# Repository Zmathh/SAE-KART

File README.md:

# SAE-KART 

Supervision d'un Kart

## Programme ESP32

### Roadmap

- Intégrer les modules testés et validés individuelement dans un même programme principal (main)

- Utilisation d'un module I2C pour la communication UART du module GPS.

- Fix les modules

### Avancée

|    Module     |     Test      |     Notes     |
| ------------- | ------------- |              -|
| MAIN ESP32    | ✅           |Terminé fonctionnel    |
| Dual Core     | ✅           |Terminé fonctionnel (1 loop/coeurs (2) )   |
| GPS           | ✅           |Terminé fonctionnel    |
| Module Lora   | ✅           |Terminé fonctionnel    |
| écran         | ✅           |Terminé fonctionnel    |
| Accel/frein   | ✅           |Terminé fonctionnel    |
| Shift register| ✅           |Terminé fonctionnel    |
| Capteur temperature|🟨       |Manque capteur temp moteur |
| I2C TO UART   | ✅           |Terminé fonctionnel    |
| Capteur fréquence| ✅  |Terminé fonctionnel   |

## SAE-KART LoRa
Simple KiCad design for an Arduino compatible RN2483 (or RN2903) LoRaWA suited for our Project.

Fork of the original [jpmeyers/RN2483shield](https://github.com/jpmeijers/RN2483shield).

***Top board view***

***Bottom board view***

Adjusted to:

 * ignore the 433MHz antenna trace (868MHz only),

### Required Parts for PCB

 * 3× 10k resistors,
 * 1× SMA 868MHz antenna,
 * 1x RN2483 (or RN2903)

### Setting up

WIP
-debug possible

### Schematic

***Schematic***

***PCB***

## Solidworks Case

***Solidworks view***

### RF Impedance Analyser Results

>(R +jX) - Calibrated with 50ohms

> The first version was a bit off, because we didn't follow the [LoRa Module Datasheet](https://ww1.microchip.com/downloads/aemDocuments/documents/OTH/ProductDocuments/DataSheets/RN2483-Low-Power-Long-Range-LoRa-Technology-Transceiver-Module-DS50002346F.pdf), where we have application information for better transmission.
Tiny holes are for [via stitching](https://www.altium.com/documentation/altium-designer/via-stitching-via-shielding-pcb) 

***[Datasheet P.12](https://ww1.microchip.com/downloads/aemDocuments/documents/OTH/ProductDocuments/DataSheets/RN2483-Low-Power-Long-Range-LoRa-Technology-Transceiver-Module-DS50002346F.pdf)***

In the end after testing we are getting better results, better signal strenght and range. So we are certainly closer for a better impedance, but it could be better as the Analyser retrieved us with not perfect transmision Impedence (29.5 +j*92.3) 
## Final result

***Final result***
## Processing 

Despite the use of an LCD arduino screen, we wanted to add a better gauge interface, more customizable so we tried to use processing.
A first sketch code has been written, using an raspberry pi with a raspberry 7" screen.

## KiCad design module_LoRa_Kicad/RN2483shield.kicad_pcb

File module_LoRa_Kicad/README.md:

# SAE-KART LoRa

Simple KiCad design for an Arduino compatible RN2483 (or RN2903) LoRaWA suited for our Project.

Fork of the original [jpmeyers/RN2483shield](https://github.com/jpmeijers/RN2483shield).

***Top board view***

***Bottom board view***

Adjusted to:

 * ignore the 433MHz antenna trace (868MHz only),

## Required Parts for PCB

 * 3× 10k resistors,
 * 1× SMA 868MHz antenna,
 * 1x RN2483 (or RN2903)

## Setting up

WIP
-debug possible

## Schematic

***Schematic***

***PCB***

# Solidworks Case

***Solidworks view***

## RF Impedance Analyser Results

>(R +jX) - Calibrated with 50ohms

> The first version was a bit off, because we didn't follow the [LoRa Module Datasheet](https://ww1.microchip.com/downloads/aemDocuments/documents/OTH/ProductDocuments/DataSheets/RN2483-Low-Power-Long-Range-LoRa-Technology-Transceiver-Module-DS50002346F.pdf), where we have application information for better transmission.
Tiny holes are for [via stitching](https://www.altium.com/documentation/altium-designer/via-stitching-via-shielding-pcb) 

***[Datasheet P.12](https://ww1.microchip.com/downloads/aemDocuments/documents/OTH/ProductDocuments/DataSheets/RN2483-Low-Power-Long-Range-LoRa-Technology-Transceiver-Module-DS50002346F.pdf)***

In the end after testing we are getting better results, better signal strenght and range. So we are certainly closer for a better impedance, but it could be better as the Analyser retrieved us with not perfect transmision Impedence (29.5 +j*92.3) 
## Final result

WIP
***Final result***
# Processing 

Despite the use of an LCD arduino screen, we wanted to add a better gauge interface, more customizable so we tried to use processing.
A first sketch code has been written, using an raspberry pi with a raspberry 7" screen.

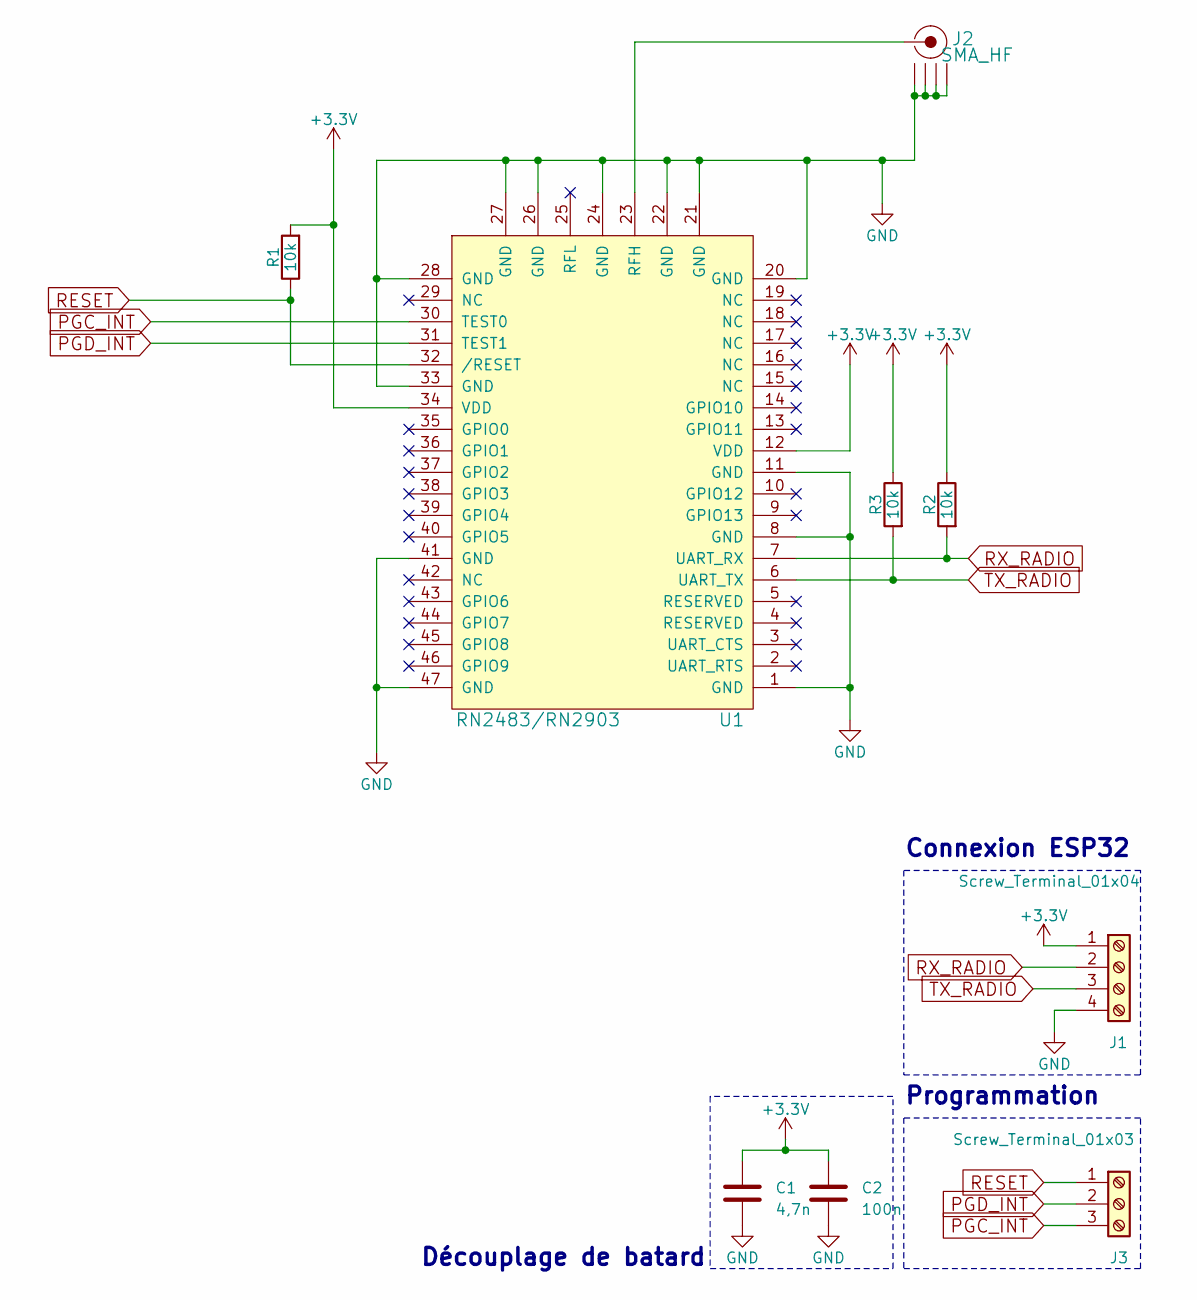
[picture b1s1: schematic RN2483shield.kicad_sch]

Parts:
C1: 4,7n; C_Disc_D3.4mm_W2.1mm_P2.50mm
C2: 100n; C_Disc_D3.4mm_W2.1mm_P2.50mm
J1: Screw_Terminal_01x04; TerminalBlock_TE_282834-4_1x04_P2.54mm_Horizontal
J2: SMA_HF; multi-rf-sma-ufl
J3: Screw_Terminal_01x03; TerminalBlock_TE_282834-3_1x03_P2.54mm_Horizontal
R1, R2, R3: 10k; R_Axial_DIN0207_L6.3mm_D2.5mm_P10.16mm_Horizontal
U1: RN2483/RN2903; RN2483

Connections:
+3V3: C1.1, C2.1, J1.1, R1.2, R2.1, R3.1, U1.12 (VDD), U1.34 (VDD)
GND: C1.2, C2.2, J1.4, J2.2 (GND1), U1.1 (GND), U1.8 (GND), U1.11 (GND), U1.20 (GND), U1.21 (GND), U1.22 (GND), U1.24 (GND), U1.26 (GND), U1.27 (GND), U1.28 (GND), U1.33 (GND), U1.41 (GND), U1.47 (GND)
unnamed: J2.1 (RF), U1.23 (RFH)
PGC_INT: J3.3, U1.30 (TEST0)
PGD_INT: J3.2, U1.31 (TEST1)
RESET: J3.1, R1.1, U1.32 (/RESET)
RX_RADIO: J1.2, R2.2, U1.7 (UART_RX)
TX_RADIO: J1.3, R3.2, U1.6 (UART_TX)

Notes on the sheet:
Connexion ESP32
Programmation
Découplage de batard

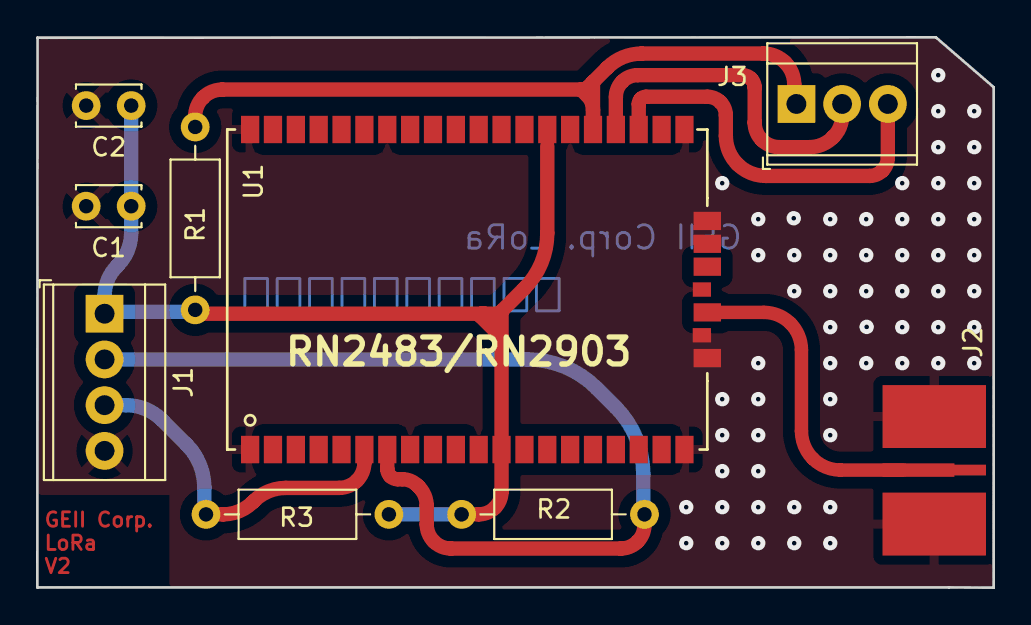
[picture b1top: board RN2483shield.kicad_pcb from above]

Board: 2 copper layers, 53.1 x 30.6 mm, 9 parts (0 on the bottom side), 8 nets.

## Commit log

2023-10-17 kicad
2023-10-17 17/10/2023
2023-10-17 commit 17/10/2023
2023-10-17 cotes
2023-11-27 27/11/2023
2023-11-27 Images updated
2023-11-27 added images
2023-11-27 Added Datasheet image
2023-11-27 Updated images
2023-11-27 Deleted images
2023-11-29 Adding images
2023-11-29 Added processing IHM_Kart
2024-01-30 adding ESP32Code
2024-01-30 ESP32Code
2024-01-30 ReadMe update
2024-01-30 final product images
2024-01-30 coucou
2024-01-30 ivan
2024-01-30 J'ai ajouter bla bla bal
2024-01-30 mathis test
2024-01-30 Ajout des petit code
2024-01-30 Ajout programme principal
2024-01-30 modif
2024-01-30 Template pour les comaintaire
2024-01-30 ajout config_h
2024-01-30 FAUTE
2024-01-30 dedoublage arduino.h
2024-01-30 deplacer
2024-01-30 Estetique
2024-01-30 ajout biblioteque Lecture_Frein_Accel + programme
2024-01-30 VITESSE_SERIAL
2024-01-30 freinaccel
2024-01-30 ajout pins header
2024-01-30 progammer
2024-01-30 sortie Lecture_Frein_Accel
2024-01-30 return
2024-01-30 folder remove
2024-01-30 serial
2024-01-30 vitesse
2024-01-30 Changement biblioteque Lecture_Frein_Accel
2024-01-30 BOOM
2024-01-30 define des varriable
2024-01-30 chinga
2024-01-30 chinfp
2024-01-30 lora
2024-01-30 Degage = et ;
2024-01-30 4 code + main
2024-01-30 samuser
2024-01-30 last 18H
2024-01-30 test
2024-01-30 Ajout des biblioteques en local
2024-01-30 MARCHE
2024-01-30 modif suppr setup/loop dans biblio
2024-01-31 Freq
2024-01-31 GPS NO MORE BROKEN
2024-01-31 Ajout Cpp Mesure_Frequece
2024-01-31 FIcher h de freq
2024-01-31 Reparation librairies LecTemp
2024-01-31 fix lectemp bug
2024-01-31 config tx rx
2024-01-31 main gps
2024-01-31 couco
2024-01-31 sup double gps
2024-01-31 include SoftwareSerial dans main
2024-01-31 SoftwareSerial library for ESP Implemented
2024-01-31 meme chose qu'avant cicular commit pour SofwareSerial
2024-01-31 j'envois
2024-01-31 Fix librairy for project
2024-01-31 BuildPath + 1ere version GPS non valide
2024-01-31 lora modif cpp
2024-01-31 lora test
2024-01-31 ajout librairie lora dans config_h
2024-01-31 Je sais pas
2024-01-31 LORA ok
2024-01-31 moi aussi je fake idle
2024-01-31 dodo
2024-02-03 je degage le temp
2024-02-03 fix build path "build" parent folder
2024-02-03 Ajout librairie écran + Mfréquence (attente librairie LiquidCrystal_I2C et Mfrequence marche pas)
2024-02-03 GPS OK pb buffer réglé
2024-02-03 Serial debug
2024-02-03 shiftReg
2024-02-03 shiftReg Ok a tester lundi
2024-02-03 shift reg main
2024-02-03 shift reg OK
2024-02-03 if endif activate
2024-02-03 config ifdef
2024-02-03 Code écran implémenté fonctionnel
2024-02-03 Ecran fonctionnel
2024-02-03 esthetique config_h
2024-02-03 ajouter entrées écran lcd
2024-02-03 Comments
2024-02-04 Implémentation du Dual Core
2024-02-04 changement delay
2024-02-05 fix Activate_Serial
2024-02-05 fix lecture temps main
2024-02-06 capteur temp test + update Readme
2024-02-06 fix ReadMe
2024-02-06 committed
2024-02-06 Revert "Update README.md"
    This reverts commit 1caf7994f3826ad360aceaefc778a23890cd18a9.
2024-02-06 fix commit
2024-02-06 fix LoRa
2024-02-06 Aceleracion/freno OK
2024-02-06 accelfrein fini
2024-02-09 ivan shift reg tests
2024-02-09 changement tentative prog freq + gps en i2c
2024-02-09 comit
2024-02-09 shift
2024-02-09 SHIFT FINITO
2024-02-13 ajout fonction delay \NOP
2024-02-13 ajout fonction delay dans main
2024-02-13 fix previous comit
2024-03-09 GPS_IIC
2024-03-09 multiple def error
2024-03-11 test 2
2024-03-16 GPS_IIC FINI
2024-03-19 Mise a jour des pins
2024-03-19 toujours mise a jour
2024-03-19 temp
2024-03-19 freq good sans serial
2024-03-20 TESTV1
2024-03-20 résolution interruptions dans programme écran ?
2024-03-21 verification pins
2024-03-21 fix pins pour uwire
2024-03-21 ATTENTION NE PAS TELEVERSER VERSION VEROLE avec temp qui marche + shiftReg
2024-03-23 test 1234
2024-03-23 vous pouvez sync
2024-03-25 frequence moyenne v1
2024-03-25 supprm lect temp
2024-03-25 boutons
2024-03-26 maconf
2024-03-26 push
2024-03-26 last
2024-03-26 calibration capteur temp avec nouvelle lib
2024-03-26 analog read batterie 12V
2024-03-26 push 18h
2024-03-26 Modification du code pour fonctionnement peut etre des boutons
2024-03-26 Commentaire du timer non utiliser
2024-03-27 push backup
2024-03-27 Modif Bouton
2024-03-27 ecran axel brieuc
2024-03-27 lora valeur
2024-03-27 lora valeurs pull
2024-03-27 Ajout DataSheet
2024-03-27 suppr nul
2024-03-27 FIX DE JESUS
2024-03-27 fix menu
2024-03-27 Modif Bouton start/stop
2024-03-29 Modif bouton fonctionnel (Version Final)
